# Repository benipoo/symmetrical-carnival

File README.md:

# symmetrical-carnival

A rudimentary nmos cpu designed from the gate level to compute the addition of two 8-bit values. 

\dKé±:}×2ôi'Tüf|#VQÏ1äíÜCøÛÆ¯W£AâÄFLfM(ÄÅEÚ:oÉÓ:zàWL¡ï1"PG±%¡y&¶ötûXõÙ½èkDÌÎB%ÚtdnGI·ÖW®·H³(!è~v¸Êyð

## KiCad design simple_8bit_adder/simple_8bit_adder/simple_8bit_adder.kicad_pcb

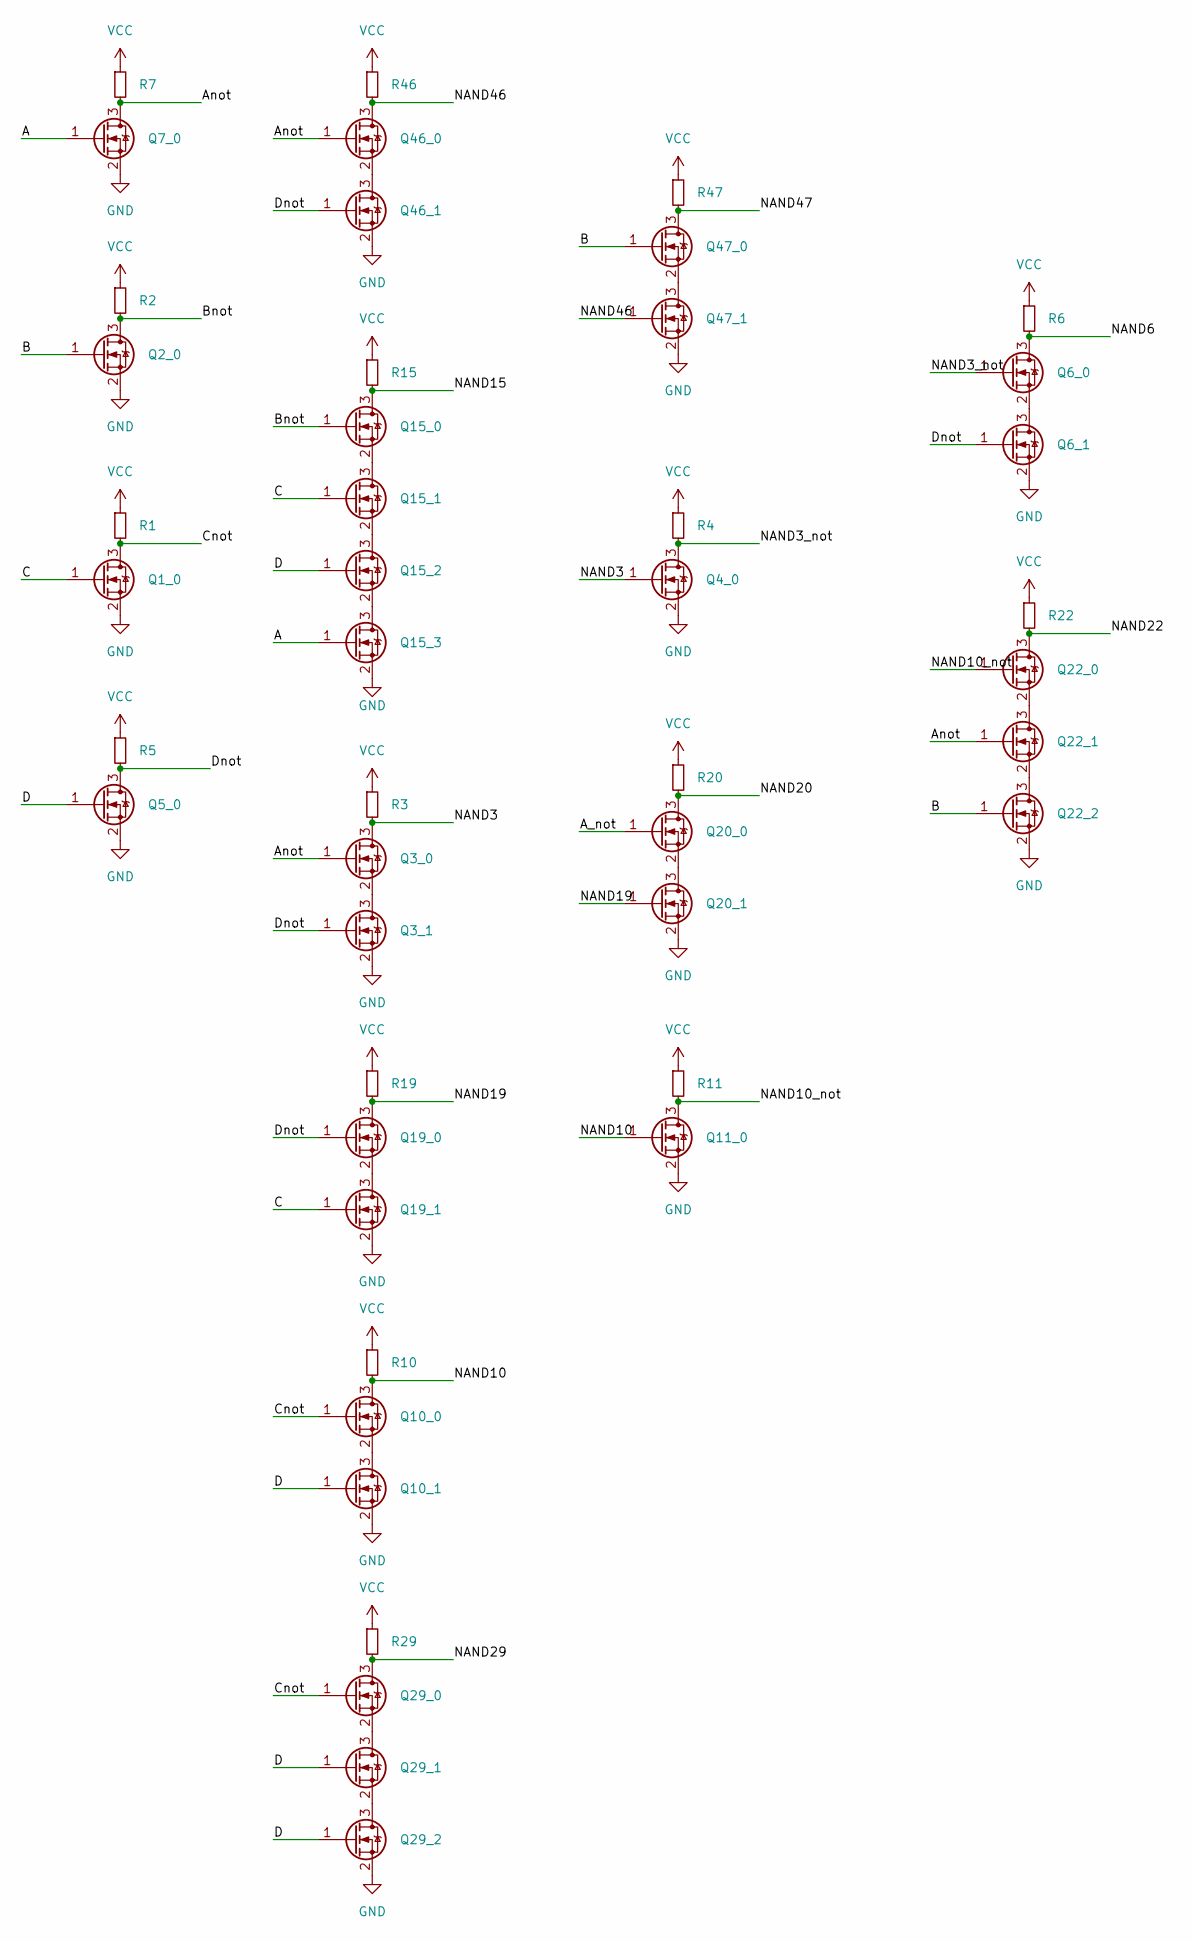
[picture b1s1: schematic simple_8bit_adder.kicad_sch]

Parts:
Q1_0, Q2_0, Q3_0, Q3_1, Q4_0, Q5_0, Q6_0, Q6_1, Q7_0, Q10_0, Q10_1, Q11_0, Q15_0, Q15_1, Q15_2, Q15_3, Q19_0, Q19_1, Q20_0, Q20_1, Q22_0, Q22_1, Q22_2, Q29_0, Q29_1, Q29_2, Q46_0, Q46_1, Q47_0, Q47_1: 2N7002; SOT-23
R1, R2, R3, R4, R5, R6, R7, R10, R11, R15, R19, R20, R22, R29, R46, R47: R_Small; R_0402_1005Metric

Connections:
/A: Q7_0.1 (G), Q15_3.1 (G)
/A_not: Q20_0.1 (G)
/Anot: Q3_0.1 (G), Q7_0.3 (D), Q22_1.1 (G), Q46_0.1 (G), R7.2
/B: Q2_0.1 (G), Q22_2.1 (G), Q47_0.1 (G); also elsewhere on the board
/Bnot: Q2_0.3 (D), Q15_0.1 (G), R2.2
/C: Q1_0.1 (G), Q15_1.1 (G), Q19_1.1 (G)
/Cnot: Q1_0.3 (D), Q10_0.1 (G), Q29_0.1 (G), R1.2
/D: Q5_0.1 (G), Q10_1.1 (G), Q15_2.1 (G), Q29_1.1 (G), Q29_2.1 (G)
/Dnot: Q3_1.1 (G), Q5_0.3 (D), Q6_1.1 (G), Q19_0.1 (G), Q46_1.1 (G), R5.2
/NAND3: Q3_0.3 (D), Q4_0.1 (G), R3.2
/NAND3_not: Q4_0.3 (D), Q6_0.1 (G), R4.2
/NAND6: Q6_0.3 (D), R6.2
/NAND10: Q10_0.3 (D), Q11_0.1 (G), R10.2
/NAND10_not: Q11_0.3 (D), Q22_0.1 (G), R11.2
/NAND15: Q15_0.3 (D), R15.2
/NAND19: Q19_0.3 (D), Q20_1.1 (G), R19.2
/NAND20: Q20_0.3 (D), R20.2
/NAND22: Q22_0.3 (D), R22.2
/NAND29: Q29_0.3 (D), R29.2
/NAND46: Q46_0.3 (D), Q47_1.1 (G), R46.2
/NAND47: Q47_0.3 (D), R47.2
GND: Q1_0.2 (S), Q2_0.2 (S), Q3_1.2 (S), Q4_0.2 (S), Q5_0.2 (S), Q6_1.2 (S), Q7_0.2 (S), Q10_1.2 (S), Q11_0.2 (S), Q15_3.2 (S), Q19_1.2 (S), Q20_1.2 (S), Q22_2.2 (S), Q29_2.2 (S), Q46_1.2 (S), Q47_1.2 (S); also elsewhere on the board
unnamed: Q3_0.2 (S), Q3_1.3 (D)
unnamed: Q6_0.2 (S), Q6_1.3 (D)
unnamed: Q10_0.2 (S), Q10_1.3 (D)
unnamed: Q15_0.2 (S), Q15_1.3 (D)
unnamed: Q15_1.2 (S), Q15_2.3 (D)
unnamed: Q15_2.2 (S), Q15_3.3 (D)
unnamed: Q19_0.2 (S), Q19_1.3 (D)
unnamed: Q20_0.2 (S), Q20_1.3 (D)
unnamed: Q22_0.2 (S), Q22_1.3 (D)
unnamed: Q22_1.2 (S), Q22_2.3 (D)
unnamed: Q29_0.2 (S), Q29_1.3 (D)
unnamed: Q29_1.2 (S), Q29_2.3 (D)
unnamed: Q46_0.2 (S), Q46_1.3 (D)
unnamed: Q47_0.2 (S), Q47_1.3 (D)
VCC: R1.1, R2.1, R3.1, R4.1, R5.1, R6.1, R7.1, R10.1, R11.1, R15.1, R19.1, R20.1, R22.1, R29.1, R46.1, R47.1; also elsewhere on the board

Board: 2 copper layers, 51 parts (0 on the bottom side), 39 nets, no tracks yet.

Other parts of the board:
Q8, Q10, Q11: 2N7002; SOT-23
R8, R9: R_Small; R_0402_1005Metric

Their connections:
/B: Q8.1 (G); also elsewhere on the board
/Q: Q10.3 (D), R8.2
GND: Q8.2 (S), Q11.2 (S); also elsewhere on the board
unnamed: Q8.3 (D), Q11.1 (G), R9.2
unnamed: Q10.2 (S), Q11.3 (D)
VCC: R8.1, R9.1; also elsewhere on the board

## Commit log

2022-11-21 added bcd_hex design files
    From Logic Friday optimizations
2022-11-21 Update README.md
    added description
2022-11-21 2to1 mux
    implemented 2to1 mux schematic
2022-11-25 added verilog
2022-11-25 made segment schematics + equations
2022-11-25 created remainder of seg files
2022-11-26 added Kicad files
2023-02-05 Template for finding ALL SMD arrangements
    Will need to be optimized to refrain from storing in memory
2023-04-22 added example files
2023-04-22 updated files
2023-04-23 optimized all files
2023-05-13 working on netlist parser
2023-05-13 adding files to parse
